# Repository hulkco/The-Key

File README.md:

The key.

It is a Breakout board for the ESP8266, with the shape of a key, which can be used as a badge.

This is an Alpha version of the PCB and may contain errors that cause it to not work properly, feel free to do all the modifications you like and your wish to share what you change.

The design is based on the product Adafruit Huzzah, and this company owns all the rights of this design.

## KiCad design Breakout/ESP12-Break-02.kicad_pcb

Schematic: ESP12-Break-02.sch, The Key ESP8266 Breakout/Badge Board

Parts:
C1: 1uF; C_0805_HandSoldering
C2, C3: 10uF; C_0805_HandSoldering
C4: 0.1uF; C_0805_HandSoldering
D1: MBR120LSFT1G; D_SOD-123
D2, D3: 1N4148; D_SOD-123
J1, J2: CONN_01X08; Pin_Header_Straight_1x08_Pitch2.54mm_SMD_Pin1Left
J3: GS2
LED1: LED-RGB-WS2812B-4SMD; WS2812B
R1, R2, R3, R5, R6, R7: 10k; R_0805_HandSoldering
RESET1: Switch; SW_SPST_B3U-1000P
U1: ESP-12; ESP-12S_SMD
U2: AP2112K-3.3TRG1; SOT-23-5_HandSoldering
USER/PROG1: Switch; SW_SPST_B3U-1000P

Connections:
/3.3V: C1.1, C3.1, C4.1, LED1.3, R1.1, R2.2, R3.2, R6.1, U1.8, U2.5 (VOUT)
/ADC: J1.2, U1.2
/CH_PD: J1.3, R1.2, U1.3
/GND: C1.2, C2.2, C3.2, C4.2, J2.8, LED1.1, R7.1, RESET1.2, U1.9, U2.2 (GND), USER/PROG1.2
/GPIO: R2.1, USER/PROG1.1
/GPIO0: J2.5, U1.12
/GPIO2: J2.6, LED1.2, R6.2, U1.11
/GPIO4: J2.4, U1.13
/GPIO5: J2.3, U1.14
/GPIO12: J1.6, U1.6
/GPIO13: J1.7, U1.7
/GPIO14: J1.5, U1.5
/GPIO15: J2.7, J3.2, R7.2, U1.10
/GPIO16: J1.4, U1.4
/RESET: D2.2, J3.1, R3.1, RESET1.1, U1.1
/RESET_5V: D2.1, J1.1
/RXD: D3.2, U1.15
/RXD_5V: D3.1, J2.2
/TXD: J2.1, U1.16
/VIN: D1.2, J1.8
unnamed: C2.1, D1.1, R5.1, U2.1 (VIN)
unnamed: R5.2, U2.3 (EN)

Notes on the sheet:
ESP8266 MODULE
POWER & FILTERING
BUTTONS & LEDS
NEOPIXEL
DEEP SLEEP

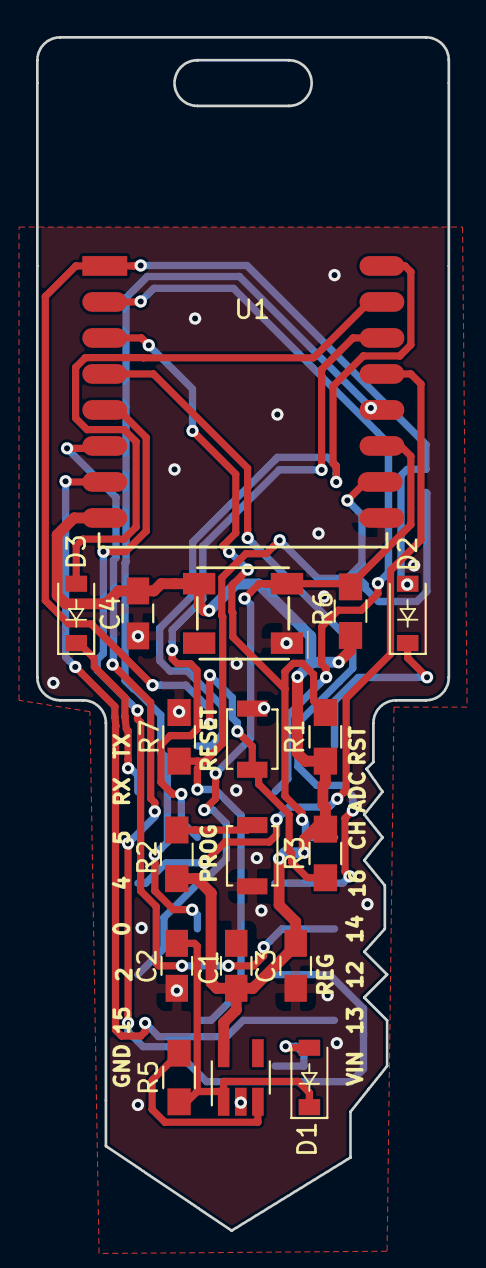
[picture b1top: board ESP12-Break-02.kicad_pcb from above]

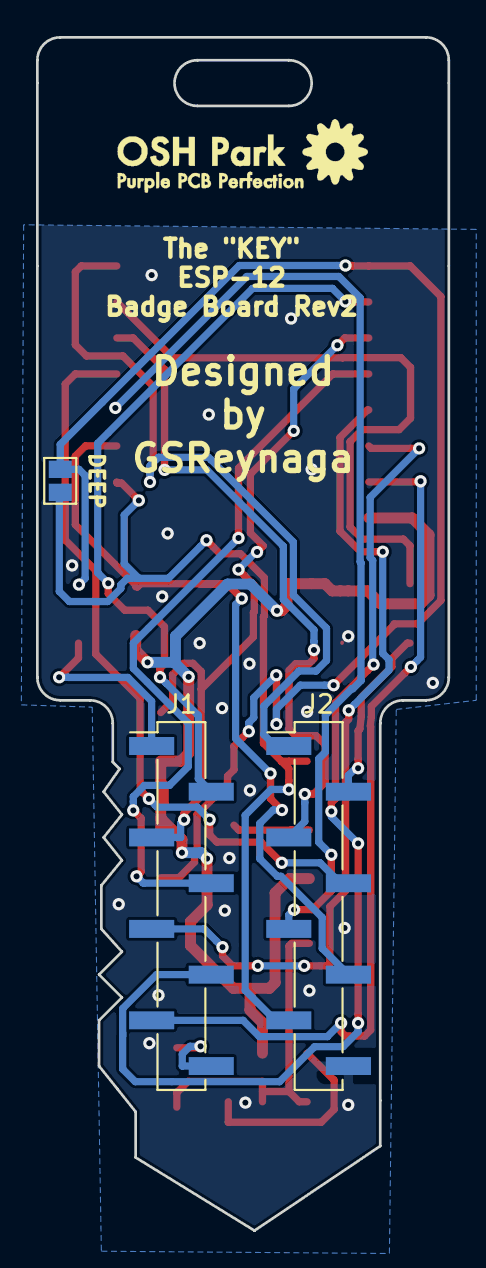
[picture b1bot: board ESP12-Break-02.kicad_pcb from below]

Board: 2 copper layers, 22.9 x 66.3 mm, 23 parts (5 on the bottom side), 22 nets.

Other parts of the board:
G2***: LOGO2; OSHpark-2-1800
G3***: LOGO3; OSHpark-1-2000

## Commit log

2018-02-24 Primera version
2018-02-24 Change value on Neopixel Capacitor
2018-02-24 Minor changes
2018-02-24 Reorganize & add USB version
2018-02-25 Star the routing process & add OshPark logo
2018-04-02 some changes
